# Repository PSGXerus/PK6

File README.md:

# Raspberry Pi 3 powered kiosk

- [Introduction](#introduction)
  - [Scope](#scope)
  - [Audience](#audience)
  - [Documentation](#documentation)
  - [Acronyms](#acronyms)
- [1. Components](#1-components)
- [2. Milestones (Roadmap)](#2-milestones-roadmap)
- [3. Software](#3-software)
- [4. Hardware](#4-hardware)
- [5. Power consumption](#5-power-consumption)
- [6. Installation](#6-installation)
- [Appendix](#appendix)
  - [Useful webpages](#useful-webpages)

## Introduction

### Scope

This repository shows the work in progress of the TI project summer 2018 no. 6. 

### Audience

This document should be a guide for future participants in the project. 

### Documentation

* [Automatic TOC generation](http://tableofcontent.eu/)
* [General form](https://docs.gitlab.com/ee/user/markdown.html)
* [Table generator](http://www.tablesgenerator.com/markdown_tables)
* Markdown editor 
	- Windows & Linux: [Ghostwriter](https://wereturtle.github.io/ghostwriter/)
	- MacOS: [Macdown](https://macdown.uranusjr.com/)

### Acronyms

**OS** Operating System

## 1. Components

| Unit         | Component                                                                          |
|:-------------|:----------------------------------------------------------------------------------:|
| Compute unit | Raspberry Pi 3 B                                                                   |
| Screen       | [Waveshare 10.1" HDMI LCD(H)](https://www.waveshare.com/wiki/10.1inch_HDMI_LCD_(H))|
| OS           | [Raspbian Stretch](https://www.raspberrypi.org/downloads/raspbian/)                |

## 2. Milestones (Roadmap)

- [x] Building development system
- [x] Putting touchscreen into operation
- [x] Creating standby logic
    - [x] Concept
    - [x] Design
    - [x] Test
- [x] Hosting a fullscreen application
	- [x] Implement button functionality
		- [x] Build button test setup
		- [x] Create python software drivers
		- [x] Solder buttons
	- [x] Set up GUI
		- [x] Implement GUI
		- [x] Test GUI on the Raspberry 
	- [x] Integration
- [x] Creating a case
	- [x] Concept
	- [x] Design
	- [x] Manufacture
	- [x] Paint
- [x] Integrating admin access
- [x] Writing setup-bashscript

## 3. Software

- Modifications on the OS can be found in [this](documentation/mods.md) document.
- The application development is descibend in [this](documentation/sw.md) document.
- The documentation for the modified bootloader can be found [here](documentation/bootloader.md).

## 4. Hardware

- Everything concerning hardware is described in [this](documentation/hw.md) document.

## 5. Power consumption

|Nominal Voltage|Measured Current|Consumed Power|
|---------------|----------------|--------------|
|12V            |~0.5A           |~6W           |

## 6. Installation

1. Download [Raspbian](https://www.raspberrypi.org/downloads/raspbian/)
2. Put a freshly formatted micro SD card into your laptop
3. Start a terminal
4. Navigate with ```cd [path]``` and ```ls``` to the folder with the downloaded Image
5. Type the following command

    ```shell
    $ sudo fdisk -l
    ```

6. Memorize the name for the SD card handle (probably /dev/mmcblk0)
7. Type this name as the \<PATH\> in this command

    **BE CAREFUL**: If \<PATH\> is not correct ```dd``` could wipe your laptops storage!!!
    
    ```shell
    $ sudo umount <PATH>
    $ sudo dd bs=1M if=./<NAME_OF_THE_IMAGE> of=<PATH>
    ```
7. Mount the SD cards boot partition
8. Add the following to the end of *cmdline.txt* on the boot partition, with \<IP\>, \<GATEWAY\> and \<BROADCAST\> set as desired

    ```
    ip=<IP>::<GATEWAY>:<BROADCAST>:rpi:eth0:off
    ```
9. Add the following to the end of *config.txt* on the boot partition

    ```
    dtoverlay=gpio-poweroff,active_low="y"
    dtoverlay=gpio-shutdown,gpio_pin=20
    ```
10. Unmount the SD card and put it into the Raspberry Pi you want to use in the kiosk
11. Boot and open a terminal
12. Use the following commands

    ```shell
    $ passwd
    # Set a password
    # Check if network is available
    $ ping 8.8.8.8
    $ git clone https://github.com/PSGXerus/PK6_2018.git
    $ cd PK6_2018/install
    $ sudo ./initialize_pi.sh &> ~/install.log
    ```

## Appendix

### Useful webpages
  
[Add a power button to the Raspberry](https://howchoo.com/g/mwnlytk3zmm/how-to-add-a-power-button-to-your-raspberry-pi)
[Original project descripton (DE)](http://www.netzmafia.de/skripten/hardware/RasPi/Projekt-Kiosk/)  
[Pi 3 Kiosk (DE)](https://itrig.de/index.php?/archives/2309-Raspberry-Pi-3-Kiosk-Chromium-Autostart-im-Vollbildmodus-einrichten.html)  
[Various Information on the Raspberry Pi (DE)](http://www.elektronik-kompendium.de/sites/raspberry-pi/index.htm)

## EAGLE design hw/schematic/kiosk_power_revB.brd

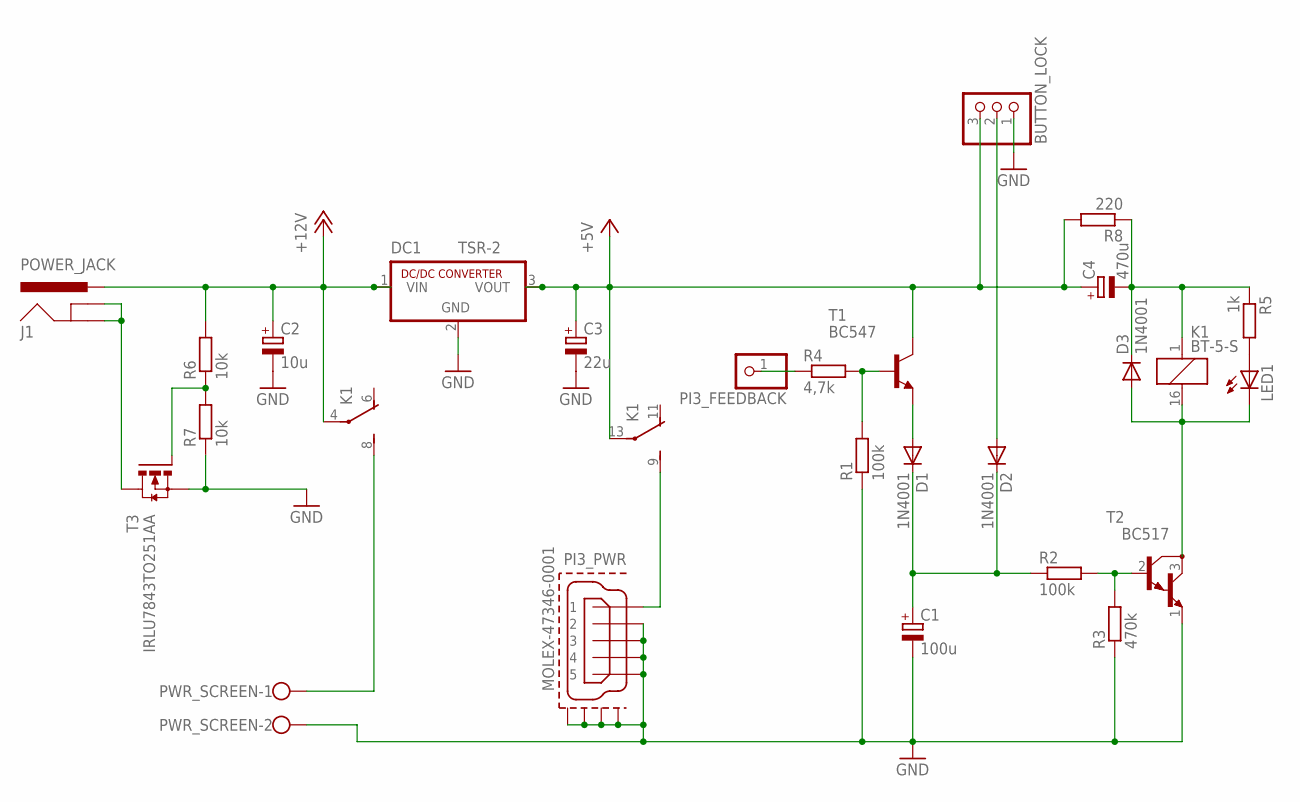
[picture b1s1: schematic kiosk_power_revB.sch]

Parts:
BUTTON_LOCK: PINHD-1X3/90; 1X03/90
C1: 100u; E2,5-5
C2: 10u; E2,5-6
C3: 22u; E2,5-5
C4: 470u; E2-5
D1, D2, D3: 1N4001; DO41-10
DC1: TSR-2; SIP3
J1: POWER_JACK; POWER_JACK_PTH
K1: BT-5-S; BT-XX-S
LED1: LED3MM
PI3_FEEDBACK: PINHD-1X1/90; 1X01/90
PI3_PWR: MOLEX-47346-0001; MOLEX-47364-0001
PWR_SCREEN: W237-102
R1, R2: 100k; 0207/7
R3: 470k; 0207/7
R4: 4,7k; 0207/7
R5: 1k; 0207/7
R6, R7: 10k; 0207/7
R8: 220; 0207/7
T1: BC547; TO92
T2: BC517; TO92
T3: IRLU7843TO251AA; TO251AA-V

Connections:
+5V: BUTTON_LOCK.3, C3.+, C4.+, DC1.3 (VOUT), K1.13, R8.2, T1.3 (C)
+12V: C2.+, DC1.1 (VIN), J1.PWR, K1.4, R6.2
GND: BUTTON_LOCK.1, C1.-, C2.-, C3.-, DC1.2 (GND), PI3_PWR.2, PI3_PWR.3, PI3_PWR.4, PI3_PWR.5, PI3_PWR.GND1, PI3_PWR.GND2, PI3_PWR.GND3, PI3_PWR.GND4, PWR_SCREEN.2, R1.1, R3.1, R7.1, T2.1 (E), T3.3 (S)
unnamed: J1.GND, J1.GNDBREAK, T3.2 (D)
unnamed: K1.8 (S), PWR_SCREEN.1
unnamed: C4.-, D3.C, K1.1, R5.1, R8.1
unnamed: PI3_FEEDBACK.1, R4.1
unnamed: K1.9 (S), PI3_PWR.1
unnamed: D3.A, K1.16 (2), LED1.K (C), T2.3 (C)
unnamed: BUTTON_LOCK.2, D2.A
unnamed: R6.1, R7.2, T3.1 (G)
unnamed: R1.2, R4.2, T1.2 (B)
unnamed: D1.A, T1.1 (E)
unnamed: C1.+, D1.C, D2.C, R2.1
unnamed: LED1.A, R5.2
unnamed: R2.2, R3.2, T2.2 (B)

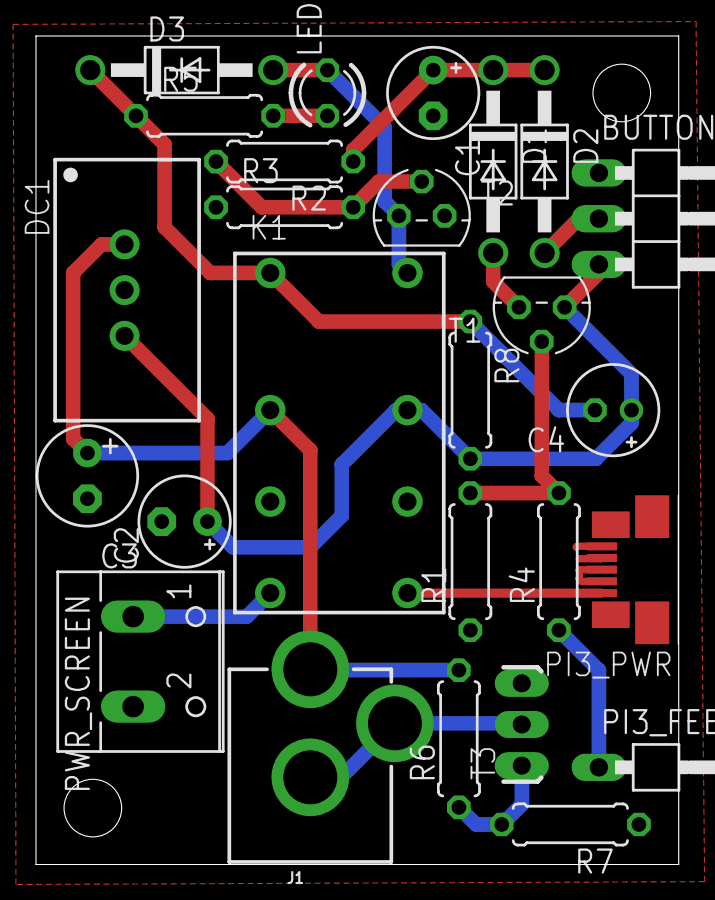
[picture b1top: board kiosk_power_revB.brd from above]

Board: 2 copper layers, 35.7 x 46.0 mm, 26 parts (0 on the bottom side), 16 nets.

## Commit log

2018-03-19 readme: Added first readme
    Added first readme for the descripton of the project.
2018-03-19 documentation: Added list of OS mods
    Added list of the mods on Raspbian needed to create
    the image for this project.
2018-03-19 readme: Fixed typo on hyperlink
2018-03-19 src: Added java files for kiosk project graphical user interface The first prototype
2018-03-20 src: Reorganized repository
    Moved java sources to different location.
2018-03-23 documentation: mods: Added uninstalls for Raspbian
    Raspbian comes with a bunch of software that is not needed.
    Added a command to the documentation which removes this software.
    Also removed the aged apt-file update command to the more recent
    apt update.
2018-03-26 documentation: mods: SSH Added SSH configuration and connection
2018-03-26 documentation: Fix MacDown allows #Title but MarkDown syntax is # Title
2018-04-03 hw: CAD: Added designs for base components
    Added designs for
    - the LCD controller
    - the LCD
    - the powerlock
    Also added a first readme for the hardware section.
2018-04-26 Skript für Drehgeber
2018-04-26 App Docu
2018-05-03 Skript für Drehgeber und Taster Funktion
2018-05-03 Logik funktionen
2018-05-03 Doku zu Taster und Drehgeber Software und Verschaltung
2018-05-03 header changes
2018-05-09 hw: CAD: Added 2 CASE designs
    Added two case designs. One made from 2 IKEA Ribba Frames
    and the other prebuilt from RND.
2018-05-09 hw: schematic: Added power board schematic
    This board is, if used with gpio_poweroff and gpio_shutdown
    DT-Overlays, capable of cutting the power to the Raspberry
    and LCD Screen after shutdown.
2018-05-09 hw: spice: Added spice simulation of Power board
    Added a basic LTSpice model for the Power board.
2018-05-09 Added gitignore for various fileformats
2018-05-13 hw: schematic: Updated schematic
    Increased relay coil series resistance to 220 ohms,
    which decreases power consumption.
2018-05-14 hw: Updated readme
    The updated readme now contains the three sections
    CAD, schematic and simulation.
2018-05-14 documentation: mods: Added bootloader modifications
    Added bootloader modifications for message supression.
    Also added two DTOs.
2018-05-15 readme: Updated
    Added hardware section to readme and updated roadmap.
2018-05-21 src: bootloader: Added debug script
    Added a script for testing the plymouth
    splash screen. It is an edited version
    of the provided script from _khAttAm_.
2018-05-21 src: bootloader: Added Raspberry Pi theme
    Added a plymouth theme which still needs
    the pngs rendered from the blender project.
2018-05-21 src: bootloader: Added blender file
    Added blender animation file
    as the source for the pngs used
    in the boot sequence.
2018-05-21 documentation: Added documentation for the bootsplash
2018-05-21 documentation: Moved hardware documentation
    Moved hardware documentation to proper
    documentation directory.
2018-05-23 Drehgeber und Taster nur ueber Interrupts. Drehgeber noch nicht getestet.
2018-05-24 test gui, funktioniert noch nicht
2018-05-30 src: bootloader: Added delay to splashscreen
    Delayed pylmouth quit on startup and improved framerate.
2018-05-30 documentation: mods: removed last messages from plymouth
2018-06-01 src: python: Logik: Removed syntax errors from interrupt reader
2018-06-01 src: python: Logik: Removed self deassert of eventcallbacks
    Removed the deassertion of the calling signal in the
    interrupt callbacks. They resulted in a segfault.
2018-06-02 src: python: Logik: Squashed the two encoder callbacks in one
    Also cleaned the python script.
2018-06-02 src: python: GUI_Test: Added additional html test files
2018-06-02 documentation: mods: Removed nasty gtk+ warnings
2018-06-02 src: python: GUI_Test: Fixed the Infoscreen script
    Fixed parallel execution in the Infoscreen script
    with the use of signals and a smaller footprint.
2018-06-04 src: python: GUT_Test: Made html change functions more versatile
    Added argument to html change functions.
    Also added listener to quit app when hitting <ESC>,
    because the app is now displayed in fullscreen mode.
2018-06-04 src: python: GUI_Test: Enabled scrolling in App
    Enabled scrolling and modified test HTML files.
2018-06-04 src: python: GUI_Test: Minor updates
    Added shebang.
    Added check of first argument.
    Fixed indexing.
2018-06-21 Bash Skript für erstmalige Systemkonfiguration
2018-06-21 src: python: GUI_Test: Fixed Infoscreen image display
    Pyqtwebview was not finding images because its
    baseurl was not set. Fixed that.
2018-06-21 documentation: mods: Added installed GUI packages.
2018-06-21 Reorganized repository
2018-06-21 update skript
2018-06-21 Skript final(nicht getestet)
2018-06-21 bash skript update
2018-06-21 hw: CAD: Updated CAD to freeCAD 0.17 and added new buttons
2018-06-21 hw: CAD: Added connector blocks to the corners of the case
2018-06-21 documentation: Migrated app.md to sw.md
2018-06-21 hw: CAD: Added technical drawings to Design
2018-06-21 readme: Updated readme
2018-06-21 update skript
    executable
2018-06-21 hw: CAD: Added paspartout document
2018-06-21 skript update
    -y bei apt
2018-06-21 hw: schematic: Added button schematic
2018-06-21 update skript
    pre boot
2018-06-21 documentation: sw: Added prototype of the software/code documenation
2018-06-21 readme: Changed the link to the software development documentation
2018-06-21 src: booloader: Updated blender file to 25fps
2018-06-21 hw: CAD: Added new mount for RJ45 connector
2018-06-21 install: Updated initialize_pi to use git directories
2018-06-21 src: bootloader: Increased wait time.
    The last value was not updated in the system.
    It was actually to short.
2018-06-21 src: bootloader: Added images for bootloader
    Also updated script and documentation.
2018-06-21 install: Deleted html directory
    For installation, the whole repository can simply be cloned.
2018-06-21 python: GUI_Test: Replaced test pictures.
2018-06-21 install: Fixed init script
2018-06-21 src: python/GUI_Test: Updated HTML test files
2018-06-21 python: GUI_Test: Added PNG images
2018-06-25 install: Fixed setup bash script and added compiled python
2018-06-25 install: Fixed executable wrapper script command
2018-06-25 install: Fixed bash script
2018-06-25 install: Made apt less noisy
    Apt has to be less noisy in order to get better logs
2018-06-25 readme: Added installation section
    Also deactivated screensaver via the bash script.
2018-06-28 install: Fixed SSH in bash script
2018-06-28 src: bootloader: Increased delay
